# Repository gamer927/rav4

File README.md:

# 1999 RAV4 Transmission Controller

**Ever wished your POS gen 1 RAV4 automatic had a shifter, so you could pretend it's a rally car?
Now you can, with this transmission mod.**

Pull the lever back: it shifts up. Push it forward: it shifts down. One click, one gear, like a
rally car's sequential gearbox. Not in the mood to row your own gears? Flip a switch and it shifts
for you: gently in **ECO**, or holding every gear to the redline in **SPORT**.

## What this is

A do-it-yourself transmission controller (a "TCU") for the **1999 Toyota RAV4 4WD** automatic
(first generation, 4-speed, 3S-FE engine). A small box under the dash, built around an Arduino
Mega, takes over the three solenoids that choose the transmission's gears. The engine, the
throttle and the engine computer stay **100 % stock**: only three wires get cut, and a plug puts
them straight back.

You build three pieces:

| Piece | Where | What it is |
|---|---|---|
| **Sequential shifter** | Centre console | A real sequential lever (the Beavis Motorsport design, 3D-printed) on a printed base |
| **Dash pod** | Dash top, driver's side | A screen, then ECO, SPORT, MANUAL, TEST and ON/OFF switches |
| **TCU box** | Under the passenger side of the dash | The Arduino and one ready-made circuit board you solder the parts onto |

**What you get:**
- **Manual mode:** you pick every gear with the lever, right up to the redline: it never
  upshifts for you, it just flashes **SHIFT UP!** on the screen. It won't let you over-rev the
  engine with a downshift.
- **Two automatic modes,** ECO and SPORT, with shift points you can tune.
- **Smarter lockup** of the torque converter: lower rpm and a cooler transmission on the highway.
- **No surprise shifts mid-corner:** a gyro holds the gear while you're turning.
- **A screen in plain English:** the gear in big numbers, the mode, and the transmission
  temperature in °F. If something's wrong, it says what, in words.
- **An aircraft-style self-test** you run from the dash, and a key-on check every time you start.

**What it takes:** about $625 in parts, a 3D printer, a soldering iron and a multimeter. You
don't need to know electronics: the [build book](docs/05-build-book.md) goes one small step at a
time, Lego-style, with a meter check after every step, and a calibration helper does the maths.

**The factory computer is always the backup.** Flip the ON/OFF switch off, lose power, or let
anything go wrong, and relays hand the transmission straight back to the factory computer. The
car then drives exactly as it did from the factory. The ON/OFF switch cuts the relays' power
**directly, in hardware**, so OFF works even if the Arduino itself has failed. How every failure
is handled, and how each one is tested, is in the [system review](docs/06-system-review.md).

## What it does and doesn't do (in real life)

**It does:**
- Let you pick every gear yourself with the lever (MANUAL), or shift for you on its own schedule
  (ECO or SPORT).
- Change **when** the transmission shifts, and when the torque converter locks up.
- Keep the converter locked more of the time: lower rpm, cooler transmission fluid, and slightly
  better mpg.
- Hold the gear through corners, and in SPORT downshift as you brake, so you're in the right gear
  for the exit.
- Show the gear, the mode and the transmission temperature, and explain any problem in words.
- Hand back to the stock car instantly (ON/OFF off), or come out completely (the BYPASS plug).

**It doesn't:**
- **Add power.** The engine, throttle and engine computer are untouched. 0–60 mph changes by a
  few tenths of a second at most. It feels more responsive, not faster.
- **Make shifts faster or firmer.** Each shift still takes about half a second, and its firmness
  is set by the transmission's own hydraulics, as stock. Shifts feel like stock shifts, just at
  different times.
- **Give engine braking from 2nd or 1st.** In D this transmission freewheels in those gears; only
  the 4→3 downshift slows the car. In MANUAL, downshifts are for holding power (corner exits,
  hills), not for slowing down.
- **Blip the throttle** on downshifts (see [rev matching](#what-about-rev-matching-on-downshifts)
  below).
- **Set off warning lights or trouble codes**, or change emissions or inspections: dummy
  resistors keep the engine computer happy.
- **Fit other cars as-is.** It's built for the 1999 RAV4 4WD automatic. Other first-generation
  RAV4 automatics are close, but check [spec §0](docs/02-revised-spec.md) first.
- **Come proven.** It hasn't been built or driven yet ([Status](#status)). Test it off public
  roads first (the build book shows how), and check your local rules and insurance.

### Day to day

You'll probably leave it in **ECO**. It drives like the stock car, only calmer: it upshifts
earlier and runs at lower rpm, so it's quieter, and the converter locks from about 23 mph, so it
feels more connected and less "slushy". Small pedal movements are smoothed out, so it doesn't
shift back and forth. Floor it and it still kicks down instantly. At very low rpm in 3rd you may
feel a slight hum; that can be tuned. **SPORT** feels sharper, not faster. **MANUAL** is the fun
one.

### MPG (estimates until it's measured on a real car)

| Driving | Compared with stock | Why |
|---|---|---|
| Steady, flat highway | about 0–2 % better | Stock already locks up in 4th at a steady cruise |
| Hills, headwinds, 70 mph and up | about 2–5 % better | Stock unlocks and slips on grades; this stays locked up to 95 % throttle |
| Town and mixed driving in ECO | about 2–6 % better | Earlier upshifts, earlier lockup, fewer extra shifts |
| SPORT or MANUAL, driven hard | worse | High rpm, on purpose |

So expect a few percent better in ECO, mostly from hills and highway speed, not a big jump. Your
right foot matters more than any mode. To measure yours, run one tank with ON/OFF off and the
next in ECO, on the same commute. Do it twice, because weather and traffic alone can swing one
tank by 5 %.

**Transmission life:** more time locked up in ECO and on the highway means less heat, and heat is
what wears out automatic transmission fluid and clutches. Driving hard in SPORT or MANUAL means
more wear, as on any car. The screen keeps an eye on the fluid temperature.

## The modes in detail

All speeds are in **mph**; the screen shows temperatures in **°F**.

Three mode switches sit on the dash: **ECO, SPORT and MANUAL. Exactly one is on at a time.** If
none is on, or two or more are, the screen says so in plain words (MODE ERROR / PICK MODE) and
the factory computer shifts until you fix it; then the box takes back over by itself. There is
no NORMAL mode: with the ON/OFF switch off, you have stock.

| Mode | Feel | What changes |
|---|---|---|
| **ECO** | Calm, economical | Early upshifts; torque-converter lockup as early as the engine can take it (from ~23 mph in 3rd), kept on when you lift for longer fuel cut, released if the engine would labour; pedal stabs ignored (0.8 s throttle smoothing). Flooring it still kicks down instantly. |
| **Highway (all modes)** | Locked and steady | In 4th above ~51 mph the torque converter stays locked up to 95 % throttle, so a long 90 mph run (~3,550 rpm) or a highway grade doesn't let it slip: lower rpm, less fuel, much less transmission heat. Only flooring it releases lockup (in SPORT, a quick stab does too). |
| **SPORT** | Sharp | Holds each gear to just under the redline at full throttle (the fastest way through these gears), kicks down from 60 % throttle, holds the gear when you snap off the throttle between corners, downshifts while braking so you're in the right gear for the exit, and releases lockup on a closed throttle or a fast pedal stab. |
| **MANUAL** | SPORT, you shift | Turn on **MANUAL** (with ECO and SPORT off), then pull or push the sequential shifter lever: one click, one gear. Same lockup and pedal response as SPORT, but the box never shifts up for you: at 6,000 rpm the screen says **SHIFT UP!** and the rest is your call (the engine computer's own fuel cut is the limit). It only downshifts by itself when you slow to a stop, so you never pull away in 4th. In ECO or SPORT the lever does nothing. |
| **STOCK** | Factory | ON/OFF off, the lever not in D, a fault, or a mode-switch mistake: the factory computer shifts, exactly as before. |
| **All automatic modes** | | No automatic shifts mid-corner (gyro), lockup off when braking. |

**Protection, always on:**
- **No over-rev:** every downshift is checked against engine rpm (refused above 5,800), and 1st
  is never allowed above 28 mph. In ECO and SPORT the box upshifts at 6,200 rpm; in MANUAL it
  tells you to (SHIFT UP!) and leaves it to you.
- **No stalling:** lockup releases when you brake and at low speed.
- **Fluid temperature:** lockup is blocked while the fluid is cold, and engages earlier when it's
  hot (110 °C+). Locking up is what cools the fluid.
- **Faults hand back to the factory computer:** a lost speed signal, a failed throttle sensor,
  bad voltage, the wrong gear engaged, a broken solenoid wire, a stuck relay, or the ON/OFF
  switch's two halves disagreeing (a broken wire in the dash cable).
- **Safe takeover:** the box only takes over after a deliberate OFF→ON flip (never by itself at
  key-on or after a reset), and only when the gear it senses from the factory computer agrees
  with the engine rpm; otherwise it waits until you stop.
- **Built-in self-test:** hold TEST for 2 s with the car parked, the engine off and ON/OFF on.
  It checks the screen, each solenoid's current, the relays, the shifter and every dash switch,
  that ON/OFF really cuts the relays by itself, and the watchdog. It refuses to run unless the
  car is parked with the engine off. A shorter relay check also runs at every key-on.
- **Locked until calibrated:** the box can't take control until you've calibrated it on your car
  (see [First steps](#first-steps)).

**Not touched:** the engine computer, the throttle, and the transmission's throttle cable.

### What about rev matching on downshifts?

True rev matching (a throttle "blip" before each downshift) needs something that can open the
throttle. The 1999 RAV4 has a cable throttle, so the box can't do it without adding a throttle
actuator. That would be a separate, safety-critical system that can accelerate the car on its
own, so this project deliberately doesn't do it.

An automatic gets the same result a different way, and the box already does it:
- **The torque converter is the rev matcher.** Before every downshift the box unlocks the
  converter clutch (200 ms ahead of the shift). The fluid coupling then absorbs the speed
  difference, which is the job a blip does in a manual gearbox.
- **Lockup stays off for 1.5 s after each shift**, so the engine settles to its new speed
  smoothly before the connection goes solid again.
- **Over-rev guard:** downshifts that would land above 5,800 rpm are refused.
- **On this transaxle, 1st and 2nd freewheel when you lift off** (one-way clutches in D). Only
  the 4→3 downshift can pull the car back with engine braking, so a downshift into 2nd or 1st
  can't jolt the car.

## Wiring

The full step-by-step guide is in **[`docs/03-wiring-guide.md`](docs/03-wiring-guide.md)**. It
covers every connector pin-out, a numbered wire list (W1–W21) matching the diagram, where each
signal is on the 1999 RAV4 with a multimeter test to confirm it, the circuit for every input,
and the build order. [`docs/wiring-detail-a.svg`](docs/wiring-detail-a.svg) is a close-up of
the solenoid changeover, which is built three times.

**The whole system is 8 cables**, each into its own labelled hole in the box:

Only three factory wires are cut (S1, S2, SL); everything else is a tap. A **bypass plug**
restores stock driving with the box removed.

**Where everything goes in the car** (TCU box, gyro, heatsink, dash pod, shifter base, ATF probe, plus the
4WD-specific notes) is [guide §9](docs/03-wiring-guide.md#9-where-everything-goes-1999-rav4-4wd).

## 3D-printed housings

Three separate pieces, each with its own cables to the TCU box. They're parametric OpenSCAD
models with ready-to-print STLs in [`hardware/`](hardware/README.md):

1. **Dash pod**, on top of the dash (driver's side): the 2.42" screen on the left, then one row of
   switches, **ECO, SPORT, MANUAL, TEST, ON/OFF** (with a flip-up safety cover). It sits on a
   small hinged mount and tilts to face you.
2. **Shifter base**, on the centre console next to the gear lever: the real
   [Beavis Motorsport sequential shifter](hardware/beavis_shifter/README.md) (by bbeavis,
   CC BY-NC) bolts on top, with its own cable to the box.
3. **TCU box**, under the passenger side of the dash where you can reach it: the Mega with the
   TCU circuit board plugged on top (it carries the gyro too). It has no switches:
   the round things on its front are eight labelled cable glands, one per cable.

A **fit check** in each model confirms that every part fits: switch bodies, terminals, wire
bends, board parts at their real heights, glands and bolts. It runs every time the STLs are
rebuilt.

Print them in **PETG or ASA, not PLA** (PLA softens in a hot car). The dummy-load resistors stay
outside on a finned heatsink. Print settings, hardware and assembly:
[`hardware/README.md`](hardware/README.md).

## Status

- **Done:** full design, firmware and documentation.
  - `make check` runs it all: 2,495 unit-test checks (with memory checkers on), 38 whole-system
    scenarios (the real firmware in a simulated car, with faults injected), a comparison of every
    screen and log line against recorded copies, 18 scenarios of the **exact .hex you flash,
    started by the Mega's real bootloader, on a simulated ATmega2560**, the calibration helper on
    a simulated drive, and 864 cross-checks that the circuit, the board (pad by pad), pin map,
    firmware, screen text and 3D models agree. All pass.
  - The tests are themselves tested: of 1,397 bugs planted one at a time in the firmware, they
    catch 100 % in the self-test, 100 % in the driving logic and 98 % in the hardware layer
    (leaving out ones that only matter exactly at a limit, and ones proven to change nothing). See the
    [system review §6](docs/06-system-review.md#6-test-results), including what only the real
    car can prove.
  - The firmware compiles for the Arduino Mega 2560 without warnings (15 % flash, 47 % RAM).
  - The screens above come from the real firmware running in a simulator.
- **Not done yet:** nothing has been built or run on real hardware or in the car. The gear
  ratios, speed-sensor scaling and throttle-sensor voltages are best estimates until you
  calibrate them (spec §8).

---

## Parts and cost

**Full shopping list, with a price estimate for every item:
[`docs/04-shopping-list.md`](docs/04-shopping-list.md)** (also as a spreadsheet:
[`shopping-list.csv`](docs/shopping-list.csv)). It lists what to buy, which store, and what to
measure on the car first so you order the right sizes once.

| | Estimate (US$, late 2026) |
|---|---|
| Brain and power (Mega, the circuit board, 5 V regulator, fuses) | $97 |
| Solenoid control (relays, MOSFETs, current sensors, dummy loads + heatsink) | $75 |
| Signal inputs (optos, comparator, chip sockets, resistors, diodes) | $17 |
| Board connectors and wire (screw terminals, pin headers) | $35 |
| Car harness and connectors (Deutsch kit with crimper, wire, shielded cable, glands) | $152 |
| Dash pod controls, OLED, gyro | $65 |
| ATF temperature probe and fittings | $59 |
| 3D printing (filament, inserts, screws) | $65 |
| Sequential shifter (Beavis Motorsport DIY) | $59 |
| **Total parts** | **≈ $625** (±25 %) |
| Tools, if you own none (your 3D printer and jack stands aren't counted) | ≈ $200 |

Many items are packs and kits, so you'll have spares. Every small electronic part comes in one
DigiKey or Mouser order, as single pieces: cheaper than packs and kits. The big-ticket items are
the connector kit with its crimper, the wire and cable, and the filament.

The key parts:

- **Arduino Mega 2560** + the **TCU circuit board** (ordered from a board maker from the files in
  [`hardware/pcb/`](hardware/pcb/README.md), about $20–40 for five). It plugs on top of the Mega
  and does all the wiring: you only solder the parts in.
- **3 × Omron G2RL-2-DC12 DPDT relays**: the factory/box changeover. Coil off = factory computer.
- **3 × IRF4905 P-MOSFETs + 3 × ACS712-05B current sensors**: switch +12 V to each solenoid
  and measure its current. (The RAV4's computer switches +12 V, so low-side MOSFET boards
  won't work.)
- **3 × 15 Ω 50 W resistors on a finned heatsink**: dummy loads, so the factory computer sees a
  "solenoid" while the box is in control. Outside the box: they make ~14 W each.
- **RECOM R-78HB5.0-0.5** 5 V regulator (72 V input), PC817 optos, LM393, ULN2803A.
- **Dash pod:** ON/OFF toggle with a flip-up cover, ECO, SPORT and MANUAL mini toggles, TEST
  button, and a **2.42" OLED** (the gear shows 18 mm tall, everything else in plain words).
- **Shifter base:** the **Beavis sequential shifter** (two V-155-1C25 switches).
- **MPU-6050 gyro (GY-521)** on the board, and a **DS18B20 ATF probe** in a brass tee.

## Tools and equipment

| Needed | Why |
|---|---|
| **Factory repair manual + electrical wiring diagram for your VIN** | To find the computer's S1/S2/SL, speed, tach, brake and lever-in-D wires, and to confirm the items in spec §10 |
| **Multimeter** with continuity beep | Every test in the build book uses it |
| **Temperature-controlled soldering iron**, solder, flux, flush cutters | About 130 parts into the circuit board |
| Wire stripper, heat gun, hot-glue gun | Harness and cables (the Deutsch kit includes its crimper) |
| **12 V 5 A DC adapter** | Bench power for testing |
| **Laptop + USB A-B cable** | Flashing the Mega and logging calibration data |
| **OBD-II scan tool** | Confirm no trouble codes are set with the box installed |
| **Four jack stands** (you have them) | Your RAV4 is full-time 4WD: **all four wheels** must be off the ground for in-gear testing |
| **3D printer** (you have one) | The housings and the shifter. 250 mm bed, or 220 mm with the no-ears TCU box |
| Drain pan, funnel, IR thermometer, phone level and GPS apps | Probe install, mounting the box flat, calibration |

## First steps

**Follow the [build book](docs/05-build-book.md)**: every step in order, from measuring the car
to the first drive, with a picture for each board step. In outline:

1. **Check the facts against your car.** Read spec [§0](docs/02-revised-spec.md) (what is
   confirmed for the 1999 RAV4) and confirm every **VERIFY** item in §10 against your repair
   manual. In particular, read the transaxle code on its ID plate.
2. **Bench test.** Build the box, connect 15 Ω resistors in place of the solenoids, and flash the
   firmware. Hold TEST to run the self-test; every line should pass. Build book part 10 walks
   through it, with a table of what to check for each failed line.
3. **Install it with the switch OFF.** In OFF, the car runs entirely on the factory computer while
   the box watches and logs over USB.
4. **Calibrate with the helper.** `tools/calibrate.py` does the maths: a 5-minute parked step
   (gas pedal, battery) and one drive with a passenger at the laptop (speed signal, gear ratios).
   It writes the numbers into `config.h`, and `calibrate.py unlock` unlocks the box once every
   step is done. Until then the ON/OFF switch is ignored and the screen shows `NOT CALIBRATED`.
5. **Test in stages** (build book part 13): jack stands with all four wheels up, then an empty
   car park, then the road.

## Documents

| Document | Contents |
|---|---|
| [`docs/03-wiring-guide.md`](docs/03-wiring-guide.md) | **Wiring guide:** connectors, wire list, where each signal is on the RAV4 and how to confirm it, circuits, build order, shifter lever |
| [`docs/wiring-diagram.svg`](docs/wiring-diagram.svg) / [`wiring-detail-a.svg`](docs/wiring-detail-a.svg) | System wiring diagram; solenoid channel close-up (regenerate with `python3 tools/wiring_diagram.py`) |
| [`docs/06-system-review.md`](docs/06-system-review.md) | **System review:** how it all fits together, every failure and what happens, the safety chain, test results, what's left |
| [`docs/02-revised-spec.md`](docs/02-revised-spec.md) | The full design: wiring, pin map, solenoid logic, every control rule, self-test, calibration, test plan |
| [`docs/oled-screens.png`](docs/oled-screens.png) | What each screen looks like |
| [`docs/05-build-book.md`](docs/05-build-book.md) | **Build book:** every step in order, Lego-instruction style, with a picture for each board step |
| [`docs/04-shopping-list.md`](docs/04-shopping-list.md) | **Shopping list** with cost estimates, by store |
| [`hardware/README.md`](hardware/README.md) | 3D-printed dash pod, shifter base and TCU enclosure: print settings, hardware, assembly, mounting |
| [`docs/01-audit.md`](docs/01-audit.md) | Review of the original spec this project started from (rev 0, which still had an oil sender and a Nextion dashboard) and what was fixed |

## Repository layout

```
firmware/tcu/tcu.ino        hardware layer: pins, inputs, relays, watchdog, screen pages, USB log
firmware/tcu/tcu_logic.*    every driving decision (no Arduino code; unit-tested on a PC)
firmware/tcu/self_test.*    built-in test: power-up, continuous and press-to-test (unit-tested)
firmware/tcu/config.h       every tunable number: shift maps, mode features, calibration
firmware/tcu/oled.*         screen driver (SSD1309 / SSD1306 / SH1106), never stalls the control loop
firmware/tcu/ds18b20.*      ATF probe driver + tested decoding
firmware/tcu/imu.*          gyro (MPU-6050) yaw-rate reader
test/                       unit tests; test/system/: whole-firmware simulation with fault injection
tools/system_check.py       cross-checks circuit, board, pins, firmware, screens and 3D models agree
tools/calibrate.py          calibration helper: records the USB log, works out the numbers
tools/avr_build.sh          compile for the Mega without the Arduino IDE
tools/wiring_diagram.py     regenerates the wiring diagrams in docs/
tools/build_stl.sh          fit-checks the housings, exports the STLs and previews in hardware/
tools/boards.py             the circuit, part by part (the one source of truth), and its checks
tools/pcb.py                the circuit board: placement, routing (pcb_router.py), DRC, Gerbers, build-book steps
tools/build_steps.py        the build book's Lego-style soldering steps and their pictures
hardware/pcb/               the KiCad board, the Gerber zip to order it, the parts list
tools/shopping_list.py      writes the shopping list and its cost totals
docs/build/                 build-book pictures (generated)
hardware/*.scad             3D-printable dash pod, shifter base and TCU enclosure (OpenSCAD)
hardware/stl/               ready-to-print STL files
LICENSE                     CC BY-NC-SA 4.0: free to build, not to sell (see the end of this page)
```

## Build and flash

```sh
make check  # everything: unit tests, system simulation, golden screens, chip test, cross-checks
            # (the chip test needs: apt install simavr libsimavr-dev)
make mutate # how good the tests are: plants bugs one at a time (a few hours)
make test   # just the unit tests on a PC (g++)
make avr    # compile for the Mega 2560 (needs: apt install gcc-avr avr-libc arduino-core-avr)
```

To flash, open `firmware/tcu/tcu.ino` in the Arduino IDE (board: **Arduino Mega 2560**) or run
`pio run -t upload` with PlatformIO. No extra libraries to install (only `Wire`, which ships with the Arduino core).

---

**Safety:** this controls the transmission of a road car. Do all early testing off public roads,
keep the ON/OFF switch within reach, and check your local regulations and insurance.

---

## License: free to build, not to sell

Copyright © 2026 gamer927. This project (firmware, tools, board layouts, 3D models, documents and
pictures) is licensed under **[CC BY-NC-SA 4.0](LICENSE)**
(Creative Commons Attribution-NonCommercial-ShareAlike). In plain words:

- ✅ **Build it, share it, change it** for your own car, and post your own version.
- ✅ **Give credit:** say it's "RAV4 TCU by gamer927", link back here and to the license, and
  say what you changed.
- ✅ **Keep it open:** anything you share that's built on this must use the same license.
- ❌ **No selling** without written permission from gamer927: not the design, kits, boards, built
  boxes, printed parts, paid downloads or paid installs. To ask, open an
  [issue](https://github.com/gamer927/rav4/issues).

The shifter's own files in [`hardware/beavis_shifter/`](hardware/beavis_shifter/README.md) are by
**bbeavis (Beavis Motorsport)** under their own Creative Commons Attribution-NonCommercial license:
credit them, and don't sell them either.

**If someone breaks the license** (sells it, or passes it off as their own): under section 6 of
the license, their permission to use it ends automatically, and from then on they're simply
infringing copyright. The copyright holder can then:
1. **Report it** to the site it's on. GitHub, Etsy, eBay, Amazon, Thingiverse and Printables all
   have a copyright (DMCA) takedown form, and they remove infringing listings.
2. **Tell them to stop** in writing.
3. **Take legal action.** In the US a copyright has to be registered before you can sue
   (copyright.gov, about $45–65). Registering within 3 months of publishing, or before the copying
   starts, also makes statutory damages and legal fees available.

**Patents.** A license can't stop someone from filing a patent, but publishing can: this design
has been public on GitHub since 26 October 2026, and every change is dated in its history. That
makes it prior art, so nobody can validly patent what's shown here. Copyright protects these
files (the code, drawings, models and documents), not the general idea: someone could still
design their own controller from scratch.

*This is a plain-English summary, not legal advice. The [LICENSE](LICENSE) file is what counts.*

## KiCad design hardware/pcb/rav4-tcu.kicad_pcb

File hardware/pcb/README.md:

# The TCU circuit board

One 2-layer board, 200 × 170 mm, that plugs straight onto the Arduino Mega and carries the
whole TCU circuit. You order it bare and solder the parts in yourself
([build book](../../docs/05-build-book.md), parts 4–6): every connection between the parts is
already a copper track, so there's no wiring on the bench.

## Ordering it

Upload **[`rav4-tcu-gerbers.zip`](rav4-tcu-gerbers.zip)** as it is (don't unzip it) to a board
maker such as JLCPCB, PCBWay, OSH Park or Aisler. Their website reads the size and the number
of layers from the zip. Pick these options:

| Option | Choose |
|---|---|
| Layers | **2** |
| Size | 200 × 170 mm (read from the zip) |
| Thickness | **1.6 mm** |
| Copper weight | **1 oz** |
| Surface finish | **HASL lead-free** (or ENIG) |
| Solder mask colour | Any. Green is usually the cheapest and fastest |
| Quantity | **5** (the usual minimum) |
| Everything else | Leave at the default. You do **not** want assembly or a stencil |

It costs about **$20–40 for five boards**, shipping included, and arrives in 1–2 weeks. Boards
over 100 × 100 mm cost a bit more at some makers. That's normal. Before you pay, look at the
maker's preview of the board: it should match the picture above, with a notch in the back-left
corner and 5 mounting holes.

## What's in this folder

| File | What it is |
|---|---|
| `rav4-tcu-gerbers.zip` | **The file to upload**: copper, solder mask, labels, outline and drill files |
| `gerbers/` | The same files unzipped, to look at in a Gerber viewer |
| `rav4-tcu.kicad_pcb`, `.kicad_pro` | The board in KiCad 7 or later, if you want to look closer or change it |
| `rav4tcu.pretty/` | The board's own footprints: the Mega's pins, the current-sensor module, the gyro module |
| `bom.csv` | Every part on the board with its reference, value and footprint |
| `drc.txt` | KiCad's design-rule check report: 0 errors and 0 unconnected pads |
| `part_fit.md` | **Will the real parts fit?** Every part checked at the largest size it's sold in: legs vs holes, bodies vs neighbours, heights. 0 problems |
| `placement.png`, `routed.png` | Pictures of where every part goes, and of every track |

The [shopping list](../../docs/04-shopping-list.md) has every part with where to buy it. The
build book's six soldering steps say which parts go in at each step.

## About the design

- **It is generated.** [`tools/pcb.py`](../../tools/pcb.py) builds the board from the tested
  circuit in [`tools/boards.py`](../../tools/boards.py): it places every part, routes every
  track with [`tools/pcb_router.py`](../../tools/pcb_router.py), fills both sides with ground,
  and refuses to write anything if KiCad's design-rule check finds an error or an unconnected
  pad. It needs KiCad 7's Python module (`python3 tools/pcb.py`). Don't edit the board by hand:
  change the script and run it again. `make check` then checks that every pad is on the net the
  circuit says.
- **Made to be easy to solder:** through-hole only, with big pads (a 0.6 mm copper ring round
  each hole where there's room, long oval pads on the chips), every part's **name and value**
  printed next to it (RU11 2.2k, DI1 1N4148…), the Mega's used pins labelled, every screw
  terminal labelled with its signal, sockets for the two bigger chips, and no ground pad joined
  solidly to the ground copper (those soak up the iron's heat).
- **Tracks sized for the current:** 1.5 mm for the solenoid supply, 1.0 mm for the solenoid,
  dummy-load and 12 V lines, 0.8 mm for the relay coils and the 5 V rail, 0.4 mm for signals.
- **The screw terminals** run along the front edge in the same order as the box's glands:
  SHIFT, DASH, SCREEN, ATF, SIG, PWR, SOL, LOAD.
- **The Mega sits underneath,** joined by plain male header strips soldered into the board. A
  notch leaves its USB and power jacks free.
- **5 V** comes from a fixed RECOM R-78HB5.0-0.5 regulator (9–72 V in): nothing to adjust.

**Nothing has been made from these files yet.** The first board you build is the first test of
the layout: check it carefully, step by step, with the build book's meter checks, and see the
[system review §8](../../docs/06-system-review.md#8-the-circuit-board).

---

*RAV4 TCU by gamer927 · [CC BY-NC-SA 4.0](../../LICENSE): free to build, not to sell. That
includes the board: you may have boards made for your own build, but not sell them.*

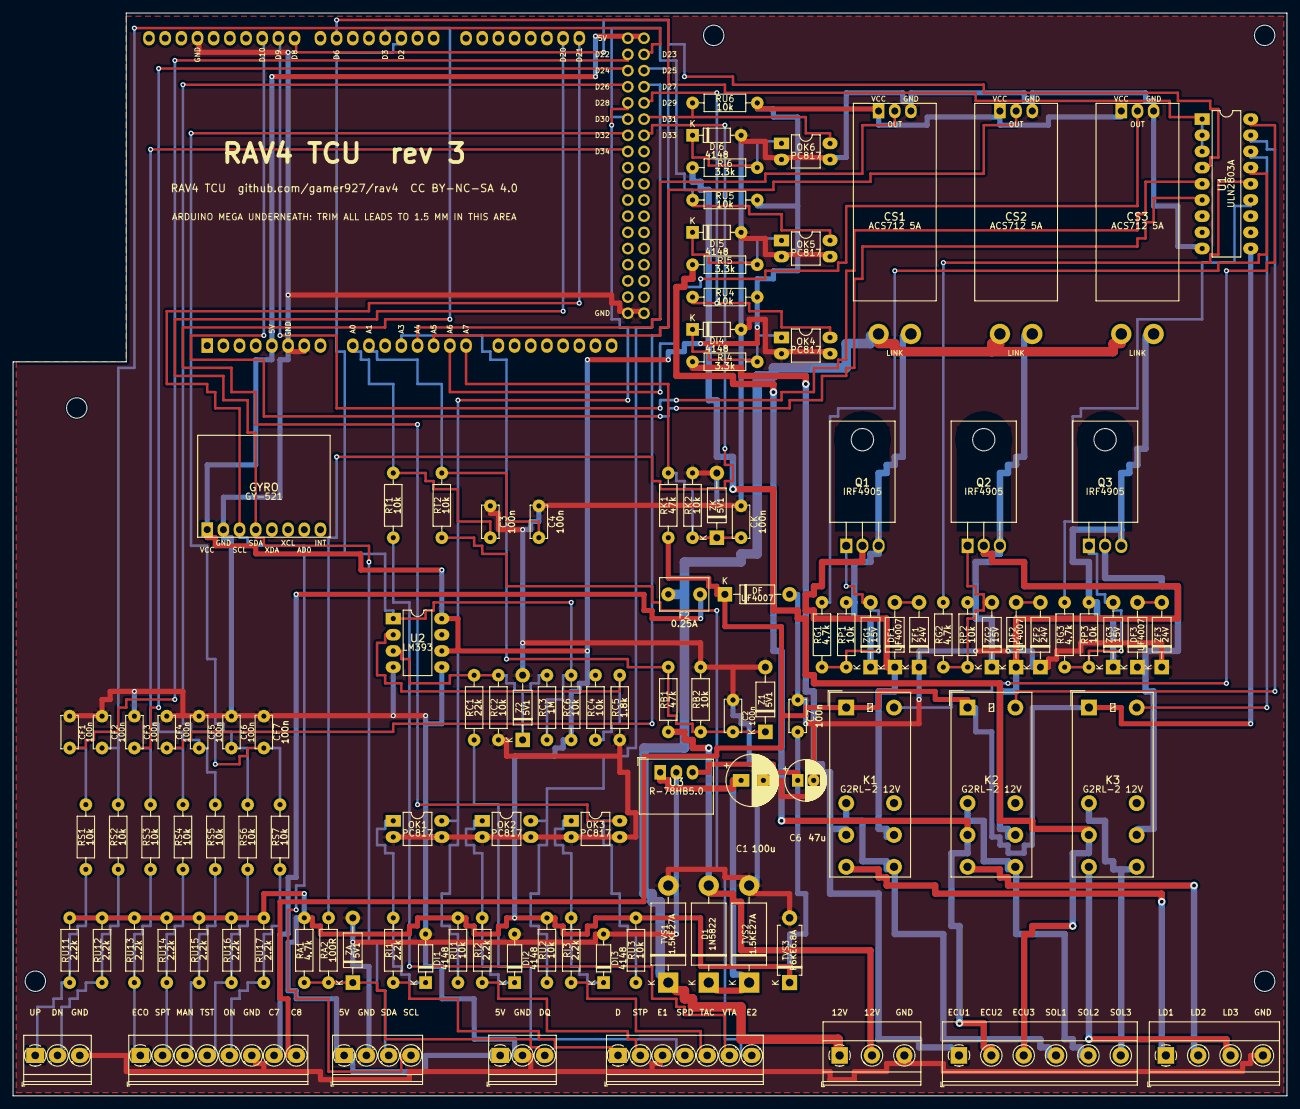
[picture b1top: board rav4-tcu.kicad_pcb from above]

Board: 2 copper layers, 200.0 x 170.0 mm, 118 parts (0 on the bottom side), 84 nets.

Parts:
A1: Arduino Mega; Arduino_Mega2560_Shield
C1: 100u; CP_Radial_D8.0mm_P3.50mm
C2, C3, C4, C7: 100n; C_Disc_D5.0mm_W2.5mm_P5.00mm
C6: 47u; CP_Radial_D6.3mm_P2.50mm
CF1, CF2, CF3, CF4, CF5, CF6, CF7: 100n; C_Disc_D5.0mm_W2.5mm_P5.00mm
CK: 100n; C_Disc_D5.0mm_W2.5mm_P5.00mm
CS1, CS2, CS3: ACS712 5A; ACS712_Module
D1: 1N5822; D_DO-201AD_P15.24mm_Horizontal
DF, DF1, DF2, DF3: UF4007; D_DO-41_SOD81_P10.16mm_Horizontal
DI1, DI2, DI3, DI4, DI5, DI6: 4148; D_DO-35_SOD27_P7.62mm_Horizontal
F2: 0.25A; C_Disc_D7.5mm_W5.0mm_P5.00mm
GYRO: GY-521; GY-521_Module
H1, H2, H3, H4, H5: MountingHole_3.2mm_M3
J1: PWR; TerminalBlock_Phoenix_MKDS-1,5-3-5.08_1x03_P5.08mm_Horizont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
J2: SOL; TerminalBlock_Phoenix_MKDS-1,5-6-5.08_1x06_P5.08mm_Horizont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
J3: SIG; TerminalBlock_Phoenix_PT-1,5-7-3.5-H_1x07_P3.50mm_Horizontal
J4: LOAD; TerminalBlock_Phoenix_MKDS-1,5-4-5.08_1x04_P5.08mm_Horizont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
K1, K2, K3: G2RL-2 12V; Relay_DPDT_Omron_G2RL-2
OK1, OK2, OK3, OK4, OK5, OK6: PC817; DIP-4_W7.62mm_LongPads
Q1, Q2, Q3: IRF4905; TO-220-3_Horizontal_TabDown
RA1: 4.7k; R_Axial_DIN0207_L6.3mm_D2.5mm_P10.16mm_Horizontal
RA2: 100R; R_Axial_DIN0207_L6.3mm_D2.5mm_P10.16mm_Horizontal
RB1: 47k; R_Axial_DIN0207_L6.3mm_D2.5mm_P10.16mm_Horizontal
RB2: 10k; R_Axial_DIN0207_L6.3mm_D2.5mm_P10.16mm_Horizontal
RC1: 22k; R_Axial_DIN0207_L6.3mm_D2.5mm_P10.16mm_Horizontal
RC2, RC4, RC6: 10k; R_Axial_DIN0207_L6.3mm_D2.5mm_P10.16mm_Horizontal
RC3: 1M; R_Axial_DIN0207_L6.3mm_D2.5mm_P10.16mm_Horizontal
RC5: 1.8k; R_Axial_DIN0207_L6.3mm_D2.5mm_P10.16mm_Horizontal
RG1, RG2, RG3: 4.7k; R_Axial_DIN0207_L6.3mm_D2.5mm_P10.16mm_Horizontal
RI1, RI2, RI3: 2.2k; R_Axial_DIN0207_L6.3mm_D2.5mm_P10.16mm_Horizontal
RI4, RI5, RI6: 3.3k; R_Axial_DIN0207_L6.3mm_D2.5mm_P10.16mm_Horizontal
RK1: 47k; R_Axial_DIN0207_L6.3mm_D2.5mm_P10.16mm_Horizontal
RK2: 10k; R_Axial_DIN0207_L6.3mm_D2.5mm_P10.16mm_Horizontal
RP1, RP2, RP3: 10k; R_Axial_DIN0207_L6.3mm_D2.5mm_P10.16mm_Horizontal
RS1, RS2, RS3, RS4, RS5, RS6, RS7: 10k; R_Axial_DIN0207_L6.3mm_D2.5mm_P10.16mm_Horizontal
RT1, RT2: 10k; R_Axial_DIN0207_L6.3mm_D2.5mm_P10.16mm_Horizontal
RU1, RU2, RU3, RU4, RU5, RU6: 10k; R_Axial_DIN0207_L6.3mm_D2.5mm_P10.16mm_Horizontal
RU11, RU12, RU13, RU14, RU15, RU16, RU17: 2.2k; R_Axial_DIN0207_L6.3mm_D2.5mm_P10.16mm_Horizontal
TVS1, TVS2: 1.5KE27A; D_DO-201AD_P15.24mm_Horizontal
TVS3: P6KE6.8A; D_DO-15_P10.16mm_Horizontal
U1: ULN2803A; DIP-18_W7.62mm_LongPads
U2: LM393; DIP-8_W7.62mm_LongPads
U3: R-78HB5.0; Converter_DCDC_RECOM_R-78HB-0.5_THT
X4: DASH; TerminalBlock_Phoenix_PT-1,5-8-3.5-H_1x08_P3.50mm_Horizontal
X5: SCREEN; TerminalBlock_Phoenix_PT-1,5-4-3.5-H_1x04_P3.50mm_Horizontal
X6: ATF; TerminalBlock_Phoenix_PT-1,5-3-3.5-H_1x03_P3.50mm_Horizontal
X7: SHIFT; TerminalBlock_Phoenix_PT-1,5-3-3.5-H_1x03_P3.50mm_Horizontal
Z1, Z2: 5V1; D_DO-41_SOD81_P10.16mm_Horizontal
ZA: 5V1; D_DO-41_SOD81_P10.16mm_Horizontal
ZF1, ZF2, ZF3: 24V; D_DO-41_SOD81_P10.16mm_Horizontal
ZG1, ZG2, ZG3: 15V; D_DO-41_SOD81_P10.16mm_Horizontal
ZK: 5V1; D_DO-41_SOD81_P10.16mm_Horizontal

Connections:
+5V: A1.5V, C6.1, C7.1, CS1.VCC, CS2.VCC, CS3.VCC, GYRO.VCC, RA1.2, RC4.2, RC6.1, RU1.2, RU2.2, RU3.2, RU4.2, RU5.2, RU6.2, RU11.2, RU12.2, RU13.2, RU14.2, RU15.2, RU16.2, RU17.2, TVS3.1, U2.6, U2.8, U3.3, X5.1, X6.1
+12_COIL: DF.1, K1.A1, K2.A1, K3.A1, RK1.1, U1.10, X4.8
+12_DRV: CS1.IP+, CS2.IP+, CS3.IP+, F2.1, J1.1, TVS1.1
+12_LOG: D1.2, J1.2, RB1.1
A0: A1.A0, C3.1, RT1.2
A1: A1.A1, C4.1, RT2.2
A3: A1.A3, C2.1, RB1.2, RB2.1, Z1.1
A4: A1.A4, CS1.OUT
A5: A1.A5, CS2.OUT
A6: A1.A6, CS3.OUT
A7: A1.A7, CK.1, RK1.2, RK2.1, ZK.1
CLAMP1: DF1.2, ZF1.2
CLAMP2: DF2.2, ZF2.2
CLAMP3: DF3.2, ZF3.2
COIL_K1: K1.A2, U1.18
COIL_K2: K2.A2, U1.17
COIL_K3: K3.A2, U1.16
D2: A1.D2, RC3.1, RC6.2, U2.1
D3: A1.D3, OK3.4, RU3.1
D6: A1.D6, U1.1, U1.2, U1.3
D8: A1.D8, U1.4
D9: A1.D9, U1.5
D10: A1.D10, U1.6
D20: A1.D20, GYRO.SDA, X5.3
D21: A1.D21, GYRO.SCL, X5.4
D22: A1.D22, CF1.1, RS1.2
D23: A1.D23, CF2.1, RS2.2
D24: A1.D24, CF3.1, RS3.2
D25: A1.D25, CF4.1, RS4.2
D26: A1.D26, CF7.1, RS7.2
D27: A1.D27, OK2.4, RU2.1
D28: A1.D28, OK1.4, RU1.1
D29: A1.D29, OK4.4, RU4.1
D30: A1.D30, OK5.4, RU5.1
D31: A1.D31, OK6.4, RU6.1
D32: A1.D32, CF6.1, RS6.2
D33: A1.D33, RA2.2
D34: A1.D34, CF5.1, RS5.2
DOUT1: DF1.1, K1.21, Q1.2
DOUT2: DF2.1, K2.21, Q2.2
DOUT3: DF3.1, K3.21, Q3.2
DQ: RA1.1, RA2.1, X6.3, ZA.1
D_in: J3.1, RI1.1
E2_in: J3.7, RT2.1
ECU_1: J2.1, K1.11, RI4.1
ECU_2: J2.2, K2.11, RI5.1
ECU_3: J2.3, K3.11, RI6.1
GATE1: Q1.1, RG1.1, RP1.1, ZG1.2
GATE2: Q2.1, RG2.1, RP2.1, ZG2.2
GATE3: Q3.1, RG3.1, RP3.1, ZG3.2
GDRV1: RG1.2, U1.15
GDRV2: RG2.2, U1.14
GDRV3: RG3.2, U1.13
GND: A1.GND, C1.2, C2.2, C3.2, C4.2, C6.2, C7.2, CF1.2, CF2.2, CF3.2, CF4.2, CF5.2, CF6.2, CF7.2, CK.2, CS1.GND, CS2.GND, CS3.GND, DF.2, DI1.2, DI2.2, DI3.2, DI4.2, DI5.2, DI6.2, GYRO.GND, J1.3, J3.3, J4.4, OK1.2, OK1.3, OK2.2, OK2.3, OK3.2, OK3.3, OK4.2, OK4.3, OK5.2, OK5.3, OK6.2, OK6.3, RB2.2, RC2.1, RC5.1, RK2.2, TVS1.2, TVS2.2, TVS3.2, U1.9, U2.4, U2.5, U3.2, X4.6, X5.2, X6.2, X7.3, Z1.2, Z2.2, ZA.2, ZF1.1, ZF2.1, ZF3.1, ZK.2
IN1_shifter_UP: RS1.1, RU11.1, X7.1
IN2_shifter_DOWN: RS2.1, RU12.1, X7.2
IN3_C1_ECO: RS3.1, RU13.1, X4.1
IN4_C2_SPORT: RS4.1, RU14.1, X4.2
IN5_C3_MANUAL: RS5.1, RU15.1, X4.3
IN6_C4_TEST: RS6.1, RU16.1, X4.4
IN7_C5_ON_OFF: RS7.1, RU17.1, X4.5
LED_OK1: DI1.1, OK1.1, RI1.2
LED_OK2: DI2.1, OK2.1, RI2.2
LED_OK3: DI3.1, OK3.1, RI3.2
LED_OK4: DI4.1, OK4.1, RI4.2
LED_OK5: DI5.1, OK5.1, RI5.2
LED_OK6: DI6.1, OK6.1, RI6.2
LOAD_1: J4.1, K1.14
LOAD_2: J4.2, K2.14
LOAD_3: J4.3, K3.14
LOG: C1.1, D1.1, TVS2.1, U3.1
REF: RC4.1, RC5.2, U2.2
SOL_1: J2.4, K1.12, K1.24
SOL_2: J2.5, K2.12, K2.24
SOL_3: J2.6, K3.12, K3.24
SPDIN: RC1.2, RC2.2, RC3.2, U2.3, Z2.1
SPD_in: J3.4, RC1.1
SRC1: CS1.IP-, Q1.3, RP1.2, ZG1.1
SRC2: CS2.IP-, Q2.3, RP2.2, ZG2.1
SRC3: CS3.IP-, Q3.3, RP3.2, ZG3.1
STP_in: J3.2, RI2.1
SWITCH_FEED: F2.2, X4.7
TAC_in: J3.5, RI3.1
VTA_in: J3.6, RT1.1

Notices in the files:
hardware/pcb/rav4-tcu.kicad_pcb:
RAV4 TCU  github.com/gamer927/rav4  CC BY-NC-SA 4.0
